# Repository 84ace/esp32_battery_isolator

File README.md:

<!-- PROJECT SHIELDS -->
<!--
*** I'm using markdown "reference style" links for readability.
*** Reference links are enclosed in brackets [ ] instead of parentheses ( ).
*** See the bottom of this document for the declaration of the reference variables
*** for contributors-url, forks-url, etc. This is an optional, concise syntax you may use.
*** https://www.markdownguide.org/basic-syntax/#reference-style-links
-->
[![Contributors][contributors-shield]][contributors-url]
[![Forks][forks-shield]][forks-url]
[![Stargazers][stars-shield]][stars-url]
[![Issues][issues-shield]][issues-url]
[![MIT License][license-shield]][license-url]
[![LinkedIn][linkedin-shield]][linkedin-url]

<!-- PROJECT LOGO -->
<br />
<p align="center">

  <h3 align="center">ESP32 Battery Isolator</h3>

  <p align="center">
    Off-road battery management
    <br />
    <a href="https://github.com/84ace/esp32_battery_isolator/wiki"><strong>Explore the docs »</strong></a>
    <br />
    <br />
    <a href="https://github.com/84ace/esp32_battery_isolator/tree/master/board_images">Board Images</a>
    ·
    <a href="https://github.com/84ace/esp32_battery_isolator/issues">Report Bug</a>
    ·
    <a href="https://github.com/84ace/esp32_battery_isolator/issues">Request Feature</a>
  </p>
</p>

<!-- TABLE OF CONTENTS -->
<details open="open">
  <summary>Table of Contents</summary>
  <ol>
    <li>
      <a href="#about-the-project">About The Project</a>
      <ul>
        <li><a href="#main-features">Main Features</a></li>
        <li><a href="#whats-missing">What's Missing</a></li>
      </ul>
    </li>
    <li>
      <a href="#get-the-isolator">Get the Isolator</a>
    </li>
    <li><a href="#roadmap">Roadmap</a></li>
    <li><a href="#contributing">Contributing</a></li>
    <li><a href="#made-with">Made with</a></li>
    <li><a href="#license">License</a></li>
    <li><a href="#contact">Contact</a></li>
    <li><a href="#acknowledgements">Acknowledgements</a></li>
  </ol>
</details>

<!-- ABOUT THE PROJECT -->
## About The Project

[![ESP32 Battery Isolator][product-screenshot]](https://github.com/84ace/esp32_battery_isolator/raw/master/enclosure/front_iso.png)

The ESP32 Battery Isolator was created so that I could have better control over battery and load isolation, and because I thought it would be an interesting project that would allow me to learn a few new things. 

I also thought that I should be able to turn the lights off in camp from the comfort of bed, rather than having to turn the lights off and walk to bed in the dark and probably kick my toe.

<!-- MAIN FEATURES -->
## Main Features:
* Dual battery input
* Triple load output
* Charger input (From external MPPT/solar charge controller)
* Current sensors
* Temperature sensor
* 128x32 OLED screen
* Bluetooth (for remote control via phone app)
* WiFi (for debugging)
* USB (micro)
* 30A continuous operation

<!-- WHAT"S MISSING -->
## What's missing:
* A Phone app for remote control / live telemetry

If you would like to contribute an app please contact me via the <a href="https://github.com/84ace/esp32_battery_isolator/tree/master/board_images">issues</a> page.

<!-- GETTING STARTED -->
## Get the Isolator

There are two ways to get started with the ESP32 Battery Isolator: 
* You can either take the easy(er) way and buy a pre-made unit from [here](https://placeholder.com/) 
* you can send the gerber files off to your favourite fab house, order the components, assemble the board and print the enclosure yourself.

Your choice!

<!-- ROADMAP -->
## Roadmap

See the [open issues](https://github.com/84ace/esp32_battery_isolator/issues) for a list of proposed features (and known issues).

<!-- CONTRIBUTING -->
## Contributing

Contributions are what make the open source community such an amazing place to be learn, inspire, and create. Any contributions you make are **greatly appreciated**.

1. Fork the Project
2. Create your Feature Branch (`git checkout -b feature/AmazingFeature`)
3. Commit your Changes (`git commit -m 'Add some AmazingFeature'`)
4. Push to the Branch (`git push origin feature/AmazingFeature`)
5. Open a Pull Request

<!-- MADE WITH -->
## Made With:
* [KiCad - Electronic Design Automation Suite](https://kicad.org/)
* [Fusion360 - CAD Software](https://www.autodesk.com.au/products/fusion-360/overview)
* [JLCPCB - PCB Fabrication Manufacturer](https://jlcpcb.com/)

<!-- LICENSE -->
## License

Distributed under the MIT License. See `LICENSE` for more information.

<!-- CONTACT -->
## Contact

84ace - [@Racea_Quigg](https://twitter.com/@RaceaQuigg)

Project Link: [https://github.com/84ace/esp32_battery_isolator](https://github.com/84ace)

<!-- MARKDOWN LINKS & IMAGES -->
<!-- https://www.markdownguide.org/basic-syntax/#reference-style-links -->
[contributors-shield]: https://img.shields.io/github/contributors/84ace/esp32_battery_isolator.svg?style=for-the-badge
[contributors-url]: https://github.com/84ace/esp32_battery_isolator/graphs/contributors
[forks-shield]: https://img.shields.io/github/forks/84ace/esp32_battery_isolator.svg?style=for-the-badge
[forks-url]: https://github.com/84ace/esp32_battery_isolator/network/members
[stars-shield]: https://img.shields.io/github/stars/84ace/esp32_battery_isolator.svg?style=for-the-badge
[stars-url]: https://github.com/84ace/esp32_battery_isolator/stargazers
[issues-shield]: https://img.shields.io/github/issues/84ace/esp32_battery_isolator.svg?style=for-the-badge
[issues-url]: https://github.com/84ace/esp32_battery_isolator/issues
[license-shield]: https://img.shields.io/github/license/84ace/esp32_battery_isolator.svg?style=for-the-badge
[license-url]: https://github.com/84ace/esp32_battery_isolator/blob/master/LICENSE.txt
[linkedin-shield]: https://img.shields.io/badge/-LinkedIn-black.svg?style=for-the-badge&logo=linkedin&colorB=555
[linkedin-url]: https://www.linkedin.com/in/acea-quigg-2007036b/
[product-screenshot]: enclosure/front_iso.png

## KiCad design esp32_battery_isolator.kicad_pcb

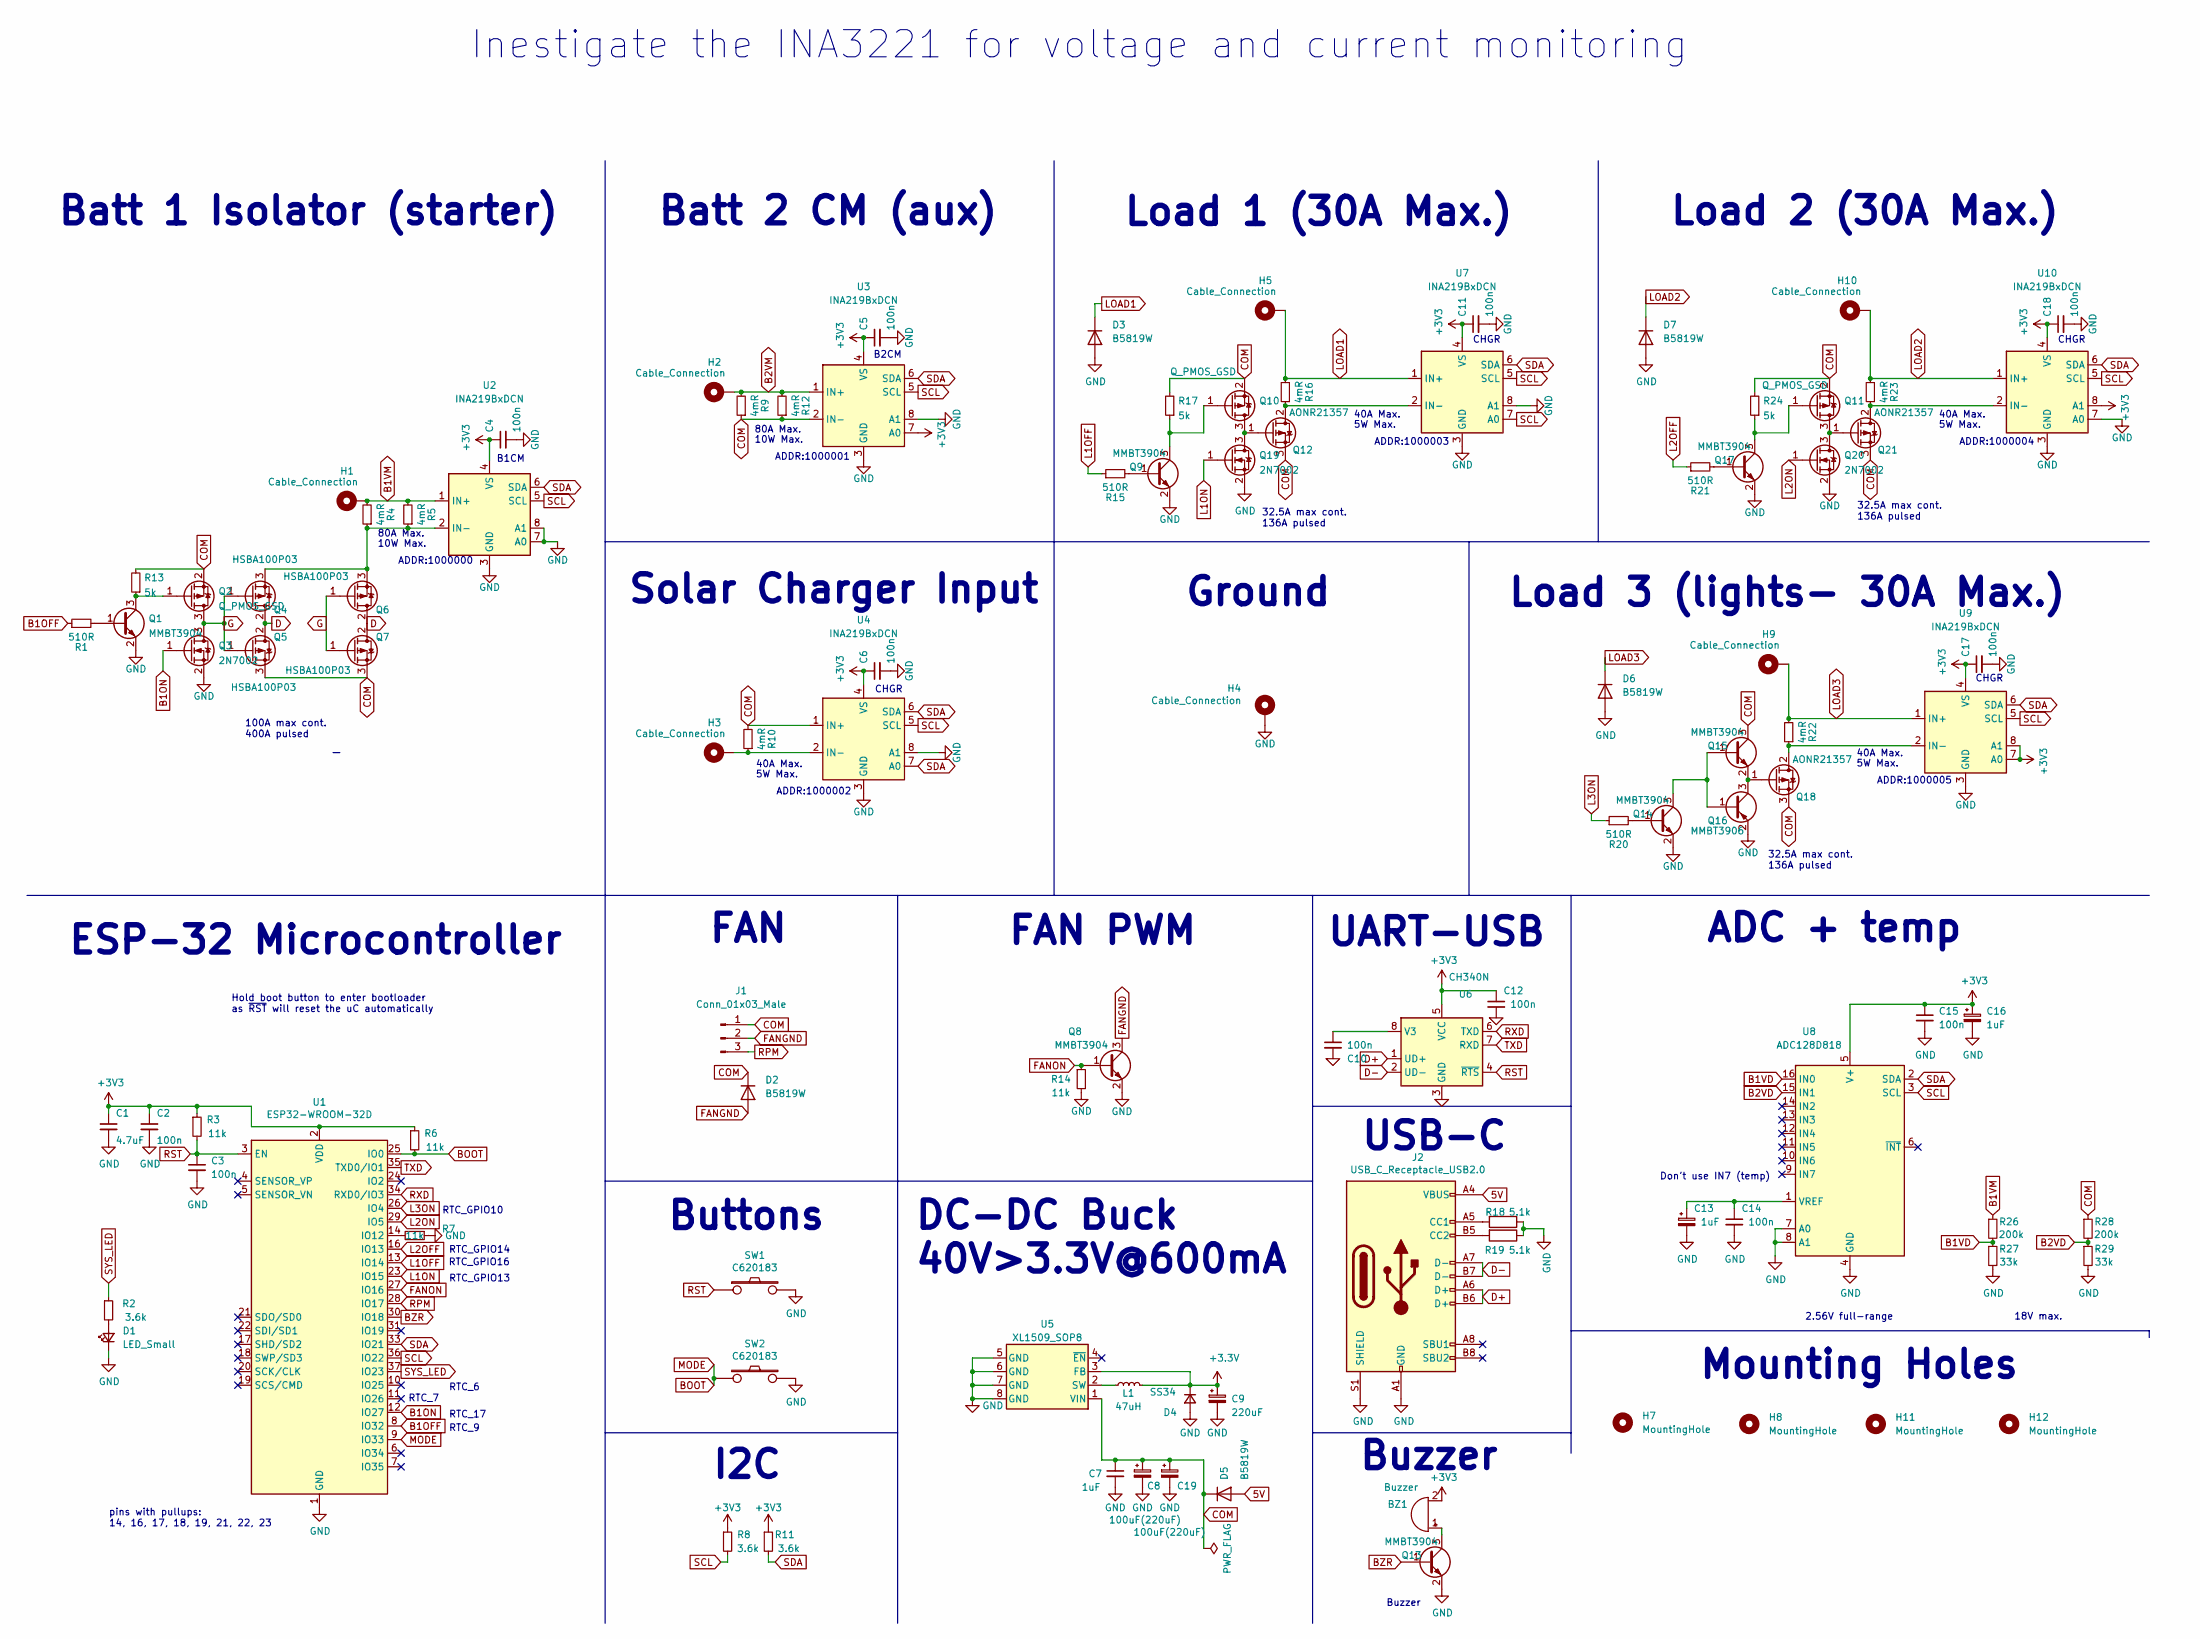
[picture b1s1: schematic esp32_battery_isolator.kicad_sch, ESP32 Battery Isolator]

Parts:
BZ1: Buzzer; SMDBuzzer_C201046; lcsc_part_number C201046
C1: 4.7uF; C_0805_2012Metric; lcsc_part_number C1779
C2, C3, C4, C5, C6, C10, C11, C12, C14, C15, C17, C18: 100n; C_0603_1608Metric; lcsc_part_number C14663
C7: 1uF; C_0603_1608Metric; lcsc_part_number C15849
C8, C19: 100uF(220uF); C_Elec_6.3x5.4; lcsc_part_number C696189
C9: 220uF; CP_EIA-3528-15_AVX-H; lcsc_part_number C30242
C13, C16: 1uF; CP_EIA-3528-21_Kemet-B; lcsc_part_number C169224
D1: LED_Small; LED_0603_1608Metric; lcsc_part_number C2286
D2, D5: B5819W; D_SOD-123; lcsc_part_number C8598
D3, D6, D7: B5819W; D_SMC; lcsc_part_number C211777
D4: SS34; D_SMA; lcsc_part_number C8678
H1, H2, H3, H4, H5, H9, H10: Cable_Connection; Rivneut_M6_Via
H7, H8, H11, H12: MountingHole; MountingHole_3.2mm_M3_Pad_Via
J1: Conn_01x03_Male; JST_SH_SM03B-SRSS-TB_1x03-1MP_P1.00mm_Horizontal; lcsc_part_number C160403
J2: USB_C_Receptacle_USB2.0; USB_C_Receptacle_HRO_TYPE-C-31-M-12; mfr_part_number TYPE-C-31-M-12; lcsc_part_number C165948
L1: 47uH; L_Bourns_SRN6045TA; lcsc_part_number C36414
Q1, Q8, Q9, Q13, Q14, Q15, Q17: MMBT3904; SOT-23; mfr_part_number MMBT3904; lcsc_part_number C20526
Q2, Q10, Q11: Q_PMOS_GSD; SOT-23
Q3, Q19, Q20: 2N7002; SOT-23
Q4, Q5, Q6, Q7: HSBA100P03; LFPAK56; lcsc_part_number C701057
Q12, Q18, Q21: AONR21357; DFN-TRANS_AONR21321; lcsc_part_number C431196
Q16: MMBT3906; SOT-23; lcsc_part_number C111114
R1, R15, R20, R21: 510R; R_0603_1608Metric; lcsc_part_number C269885
R2, R8, R11: 3.6k; R_0603_1608Metric; lcsc_part_number C22980
R3, R6, R7, R14: 11k; R_0603_1608Metric; lcsc_part_number C25950
R4, R5, R9, R10, R12, R16, R22, R23: 4mR; RS1050Metric_Pad5.3x2.5mm; lcsc_part_number C481476
R13, R17, R24: 5k; R_0603_1608Metric; lcsc_part_number C269885
R18, R19: 5.1k; R_0603_1608Metric; mfr_part_number RS-03K5101FT; lcsc_part_number C156350
R26, R28: 200k; R_0603_1608Metric; lcsc_part_number C25811
R27, R29: 33k; R_0603_1608Metric; lcsc_part_number C4216
SW1, SW2: C620183; TS4550TP; lcsc_part_number C620183
U1: ESP32-WROOM-32D; ESP32-WROOM-32; mfr_part_number ESP32-WROOM-32D; lcsc_part_number C473012
U2, U3, U4, U7, U9, U10: INA219BxDCN; SOT-23-8; lcsc_part_number C2155693
U5: XL1509_SOP8; SOIC-8_3.9x4.9mm_P1.27mm; lcsc_part_number C2681226
U6: CH340N; SOIC-8_3.9x4.9mm_P1.27mm; mfr_part_number CH340N; lcsc_part_number C506813
U8: ADC128D818; TSSOP-16_4.4x5mm_P0.65mm; mfr_part_number ADC128D818CIMTX; lcsc_part_number C139062

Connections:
5V: D5.2 (A), J2.A4 (VBUS), J2.A9 (VBUS), J2.B4 (VBUS), J2.B9 (VBUS)
B1OFF: R1.1, U1.8 (IO32)
B1ON: Q3.1 (G), U1.12 (IO27)
B1VD: R26.2, R27.1, U8.16 (IN0)
B1VM: H1.1, R4.2, R5.2, R26.1, U2.1 (IN+)
B2VD: R28.2, R29.1, U8.15 (IN1)
B2VM: H2.1, R9.2, R12.2, U3.1 (IN+)
BOOT: R6.2, SW2.1, U1.9 (IO33), U1.25 (IO0)
BZR: Q13.1 (B), U1.30 (IO18)
COM: C7.1, C8.1, C19.1, D2.1 (K), D5.1 (K), J1.1, Q2.2 (S), Q5.3 (S), Q7.3 (S), Q10.2 (S), Q11.2 (S), Q12.3 (S), Q15.3 (C), Q18.3 (S), Q21.3 (S), R9.1, R10.2, R12.1, R13.2, R17.2, R24.2, R28.1, U3.2 (IN-), U4.1 (IN+), U5.1 (VIN)
D: Q4.2 (D), Q5.2 (D), Q6.2 (D), Q7.2 (D)
D+: J2.A6 (D+), J2.B6 (D+), U6.1 (UD+)
D-: J2.A7 (D-), J2.B7 (D-), U6.2 (UD-)
FANGND: D2.2 (A), J1.2, Q8.3 (C)
FANON: Q8.1 (B), R14.1, U1.27 (IO16)
G: Q2.3 (D), Q3.3 (D), Q4.1 (G), Q5.1 (G), Q6.1 (G), Q7.1 (G)
GND: C1.2, C2.2, C3.2, C4.2, C5.2, C6.2, C7.2, C8.2, C9.2, C10.2, C11.2, C12.2, C13.2, C14.2, C15.2, C16.2, C17.2, C18.2, C19.2, D1.1 (K), D3.2 (A), D4.2 (A), D6.2 (A), D7.2 (A), H4.1, J2.A1 (GND), J2.A12 (GND), J2.B1 (GND), J2.B12 (GND), J2.S1 (SHIELD), Q1.2 (E), Q3.2 (S), Q8.2 (E), Q9.2 (E), Q13.2 (E), Q14.2 (E), Q16.2 (E), Q17.2 (E), Q19.2 (S), Q20.2 (S), R7.1, R14.2, R18.1, R19.1, R27.2, R29.2, SW1.2, SW2.2, U1.1 (GND), U1.15 (GND), U1.38 (GND), U1.39 (GND), U2.3 (GND), U2.7 (A0), U2.8 (A1), U3.3 (GND), U3.8 (A1), U4.3 (GND), U4.8 (A1), U5.5 (GND), U5.6 (GND), U5.7 (GND), U5.8 (GND), U6.3 (GND), U7.3 (GND), U7.8 (A1), U8.4 (GND), U8.7 (A0), U8.8 (A1), U9.3 (GND), U10.3 (GND), U10.7 (A0)
L1OFF: R15.1, U1.13 (IO14)
L1ON: Q19.1 (G), U1.23 (IO15)
L2OFF: R21.1, U1.16 (IO13)
L2ON: Q20.1 (G), U1.29 (IO5)
L3ON: R20.1, U1.26 (IO4)
LOAD1: D3.1 (K), H5.1, R16.2, U7.1 (IN+)
LOAD2: D7.1 (K), H10.1, R23.2, U10.1 (IN+)
LOAD3: D6.1 (K), H9.1, R22.2, U9.1 (IN+)
unnamed: BZ1.1 (-), Q13.3 (C)
unnamed: D1.2 (A), R2.2
unnamed: J2.A5 (CC1), R18.2
unnamed: J2.B5 (CC2), R19.2
unnamed: Q1.1 (B), R1.2
unnamed: Q1.3 (C), Q2.1 (G), R13.1
unnamed: Q4.3 (S), Q6.3 (S), R4.1, R5.1, U2.2 (IN-)
unnamed: Q9.1 (B), R15.2
unnamed: Q10.3 (D), Q12.1 (G), Q19.3 (D)
unnamed: Q9.3 (C), Q10.1 (G), R17.1
unnamed: Q11.3 (D), Q20.3 (D), Q21.1 (G)
unnamed: Q11.1 (G), Q17.3 (C), R24.1
unnamed: Q12.2 (D), R16.1, U7.2 (IN-)
unnamed: Q14.1 (B), R20.2
unnamed: Q14.3 (C), Q15.1 (B), Q16.1 (B)
unnamed: Q15.2 (E), Q16.3 (C), Q18.1 (G)
unnamed: Q17.1 (B), R21.2
unnamed: Q18.2 (D), R22.1, U9.2 (IN-)
unnamed: Q21.2 (D), R23.1, U10.2 (IN-)
unnamed: R7.2, U1.14 (IO12)
unnamed: H3.1, R10.1, U4.2 (IN-)
unnamed: L1.1, U5.2 (SW)
unnamed: C10.1, U6.8 (V3)
unnamed: C13.1, C14.1, U8.1 (VREF)
RPM: J1.3, U1.28 (IO17)
RST: C3.1, R3.2, SW1.1, U1.3 (EN), U6.4 (~RTS)
RXD: U1.34 (RXD0/IO3), U6.6 (TXD)
SCL: R8.2, U1.36 (IO22), U2.5 (SCL), U3.5 (SCL), U4.5 (SCL), U7.5 (SCL), U7.7 (A0), U8.3 (SCL), U9.5 (SCL), U10.5 (SCL)
SDA: R11.2, U1.33 (IO21), U2.6 (SDA), U3.6 (SDA), U4.6 (SDA), U4.7 (A0), U7.6 (SDA), U8.2 (SDA), U9.6 (SDA), U10.6 (SDA)
SYS_LED: R2.1, U1.37 (IO23)
TXD: U1.35 (TXD0/IO1), U6.7 (RXD)

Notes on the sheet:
RTC_GPIO10
Mounting Holes
40A Max.
Ground
5W Max.
32.5A max cont. 136A pulsed
B2CM
ADDR:1000001
RTC_7
ADDR:1000003
I2C
Hold boot button to enter bootloader as ~{RST} will reset the uC automatically
Inestigate the INA3221 for voltage and current monitoring
ESP-32 Microcontroller
UART-USB
10W Max.
DC-DC Buck 40V>3.3V@600mA
Load 3 (lights- 30A Max.)
ADDR:1000005
ADDR:1000004
Buttons
CHGR
80A Max.
ADDR:1000000
B1CM
RTC_9
ADDR:1000002
Don’t use IN7 (temp)
2.56V full-range
RTC_6
100A max cont. 400A pulsed
Load 2 (30A Max.)
pins with pullups: 14, 16, 17, 18, 19, 21, 22, 23
FAN
RTC_GPIO16
RTC_GPIO14
RTC_17
Batt 1 Isolator (starter)
Solar Charger Input
ADC + temp

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
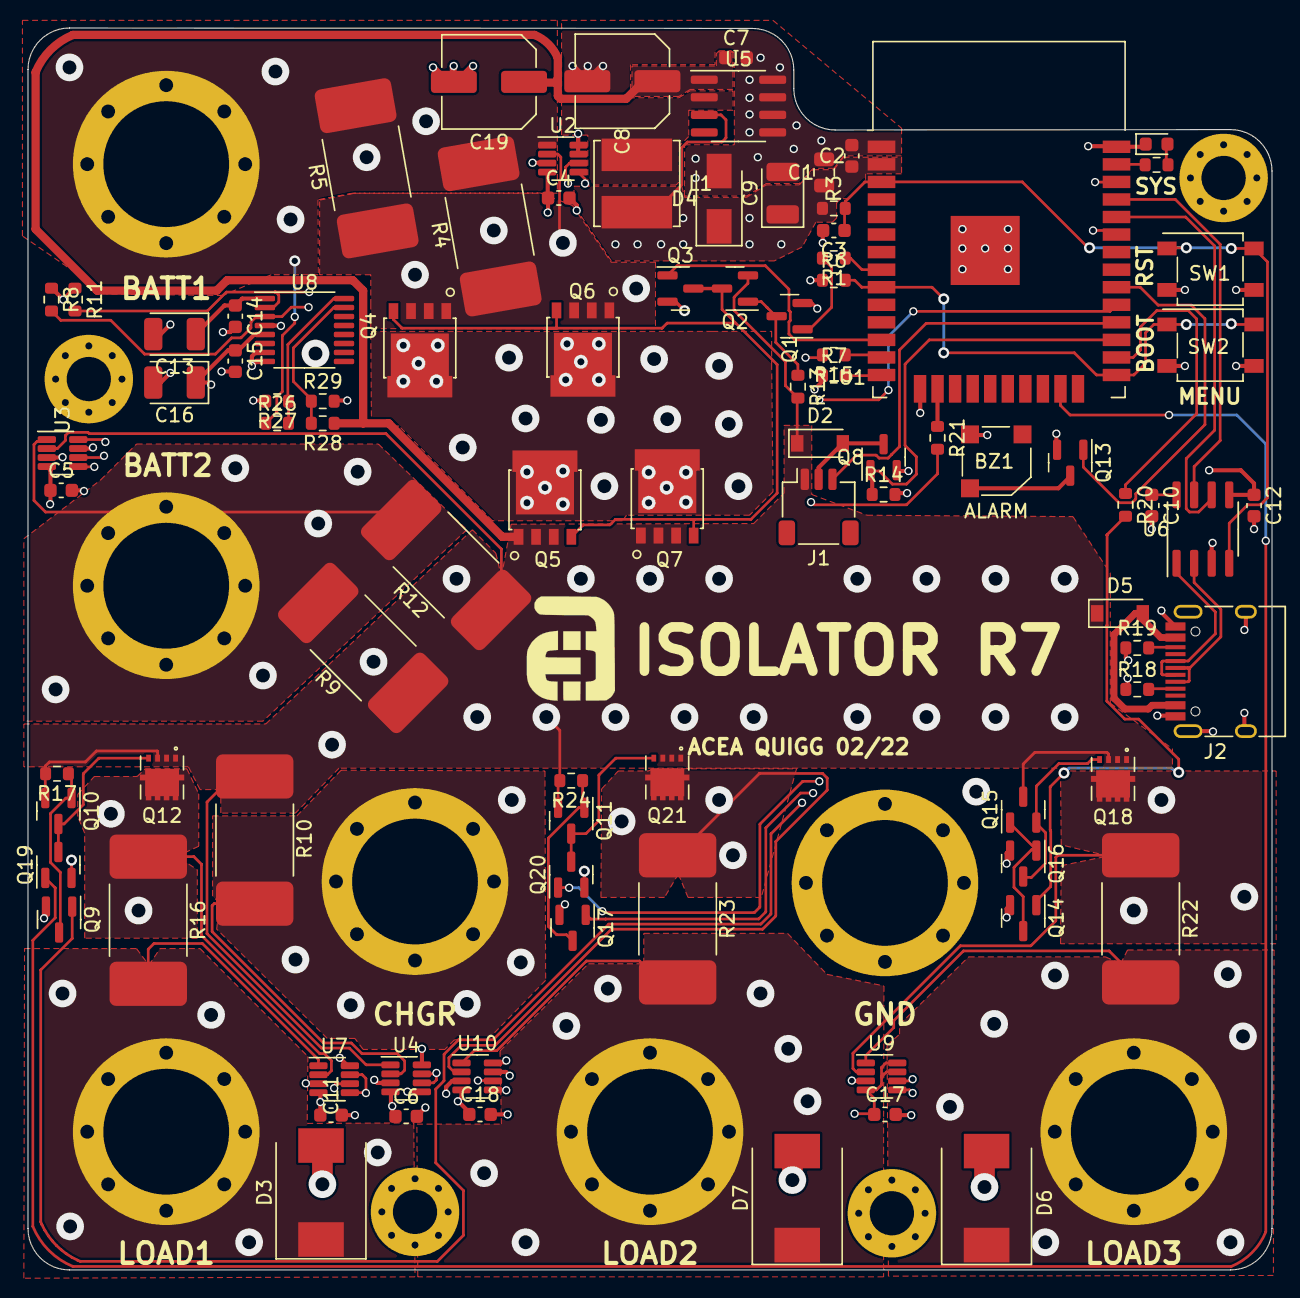
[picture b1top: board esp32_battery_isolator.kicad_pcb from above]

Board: 4 copper layers, 90.0 x 89.9 mm, 103 parts (0 on the bottom side), 57 nets.

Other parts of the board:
Ref**: Val**; aces_electronics_small

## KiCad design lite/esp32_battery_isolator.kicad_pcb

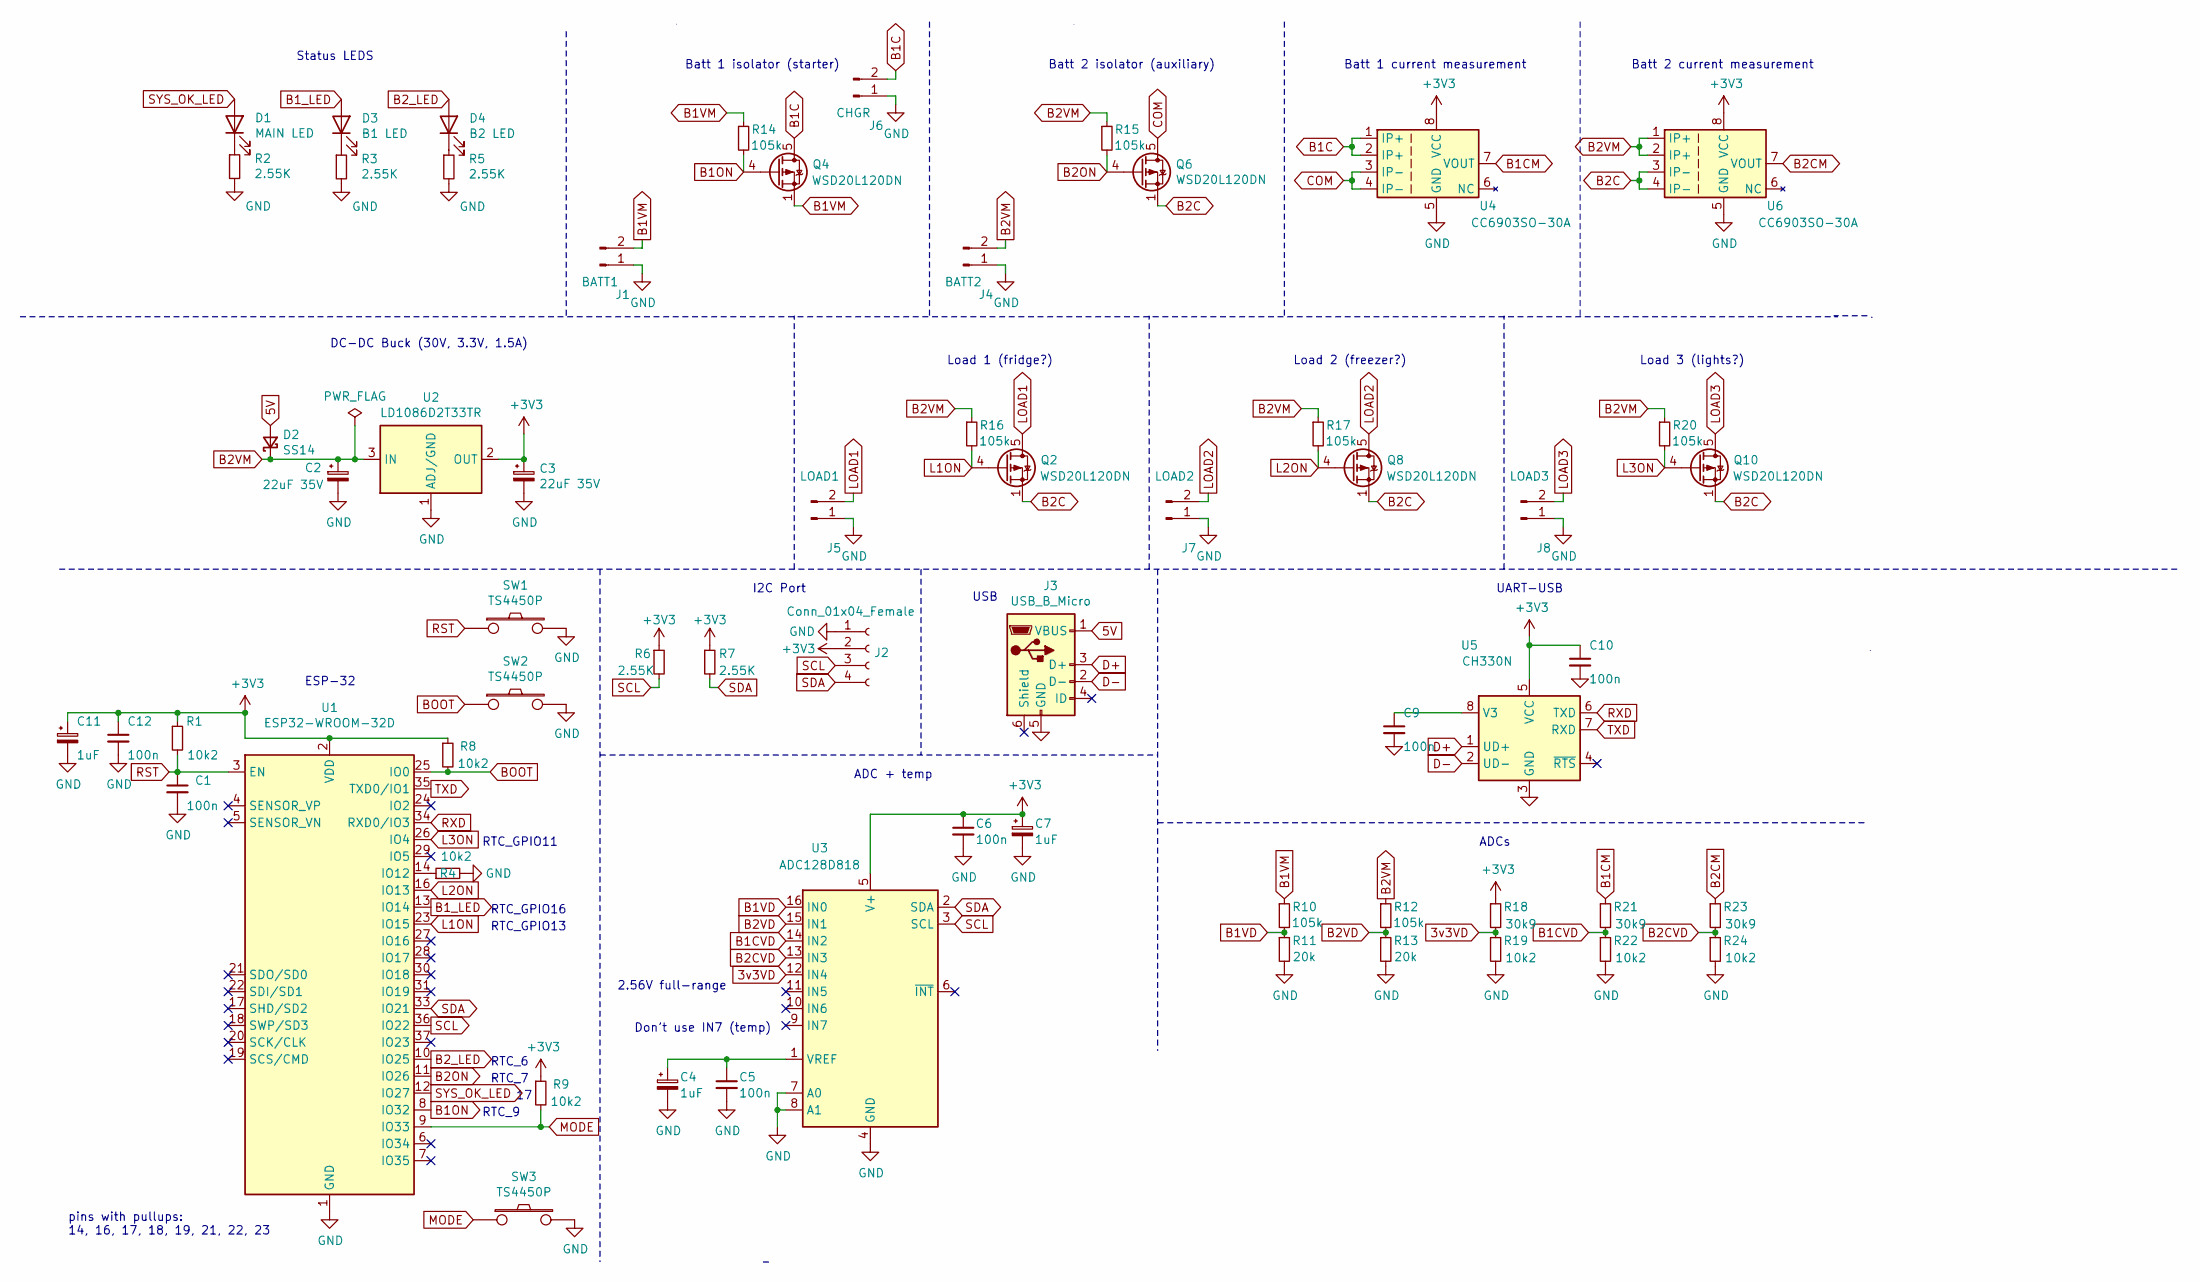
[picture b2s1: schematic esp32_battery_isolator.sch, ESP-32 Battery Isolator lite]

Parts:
C1, C5, C6, C9, C10, C12: 100n; C_0805_2012Metric; mfr_part_number 0805B104K250; lcsc_part_number C128353
C2, C3: 22uF 35V; C_Elec_5x5.4; mfr_part_number RVT1V220M0505; lcsc_part_number C23289
C4, C7, C11: 1uF; CP_EIA-3216-18_Kemet-A; mfr_part_number CA45-A035K105T; lcsc_part_number C126949
D1: MAIN LED; LED_0603_1608Metric; mfr_part_number 19-217/R6C-AL1M2VY/3T; lcsc_part_number C72044
D2: SS14; D_SMA; mfr_part_number SS14; lcsc_part_number C2480
D3: B1 LED; LED_0603_1608Metric; mfr_part_number 19-217/R6C-AL1M2VY/3T; lcsc_part_number C72044
D4: B2 LED; LED_0603_1608Metric; mfr_part_number 19-217/R6C-AL1M2VY/3T; lcsc_part_number C72044
J1: BATT1; AMASS_XT60-F_1x02_P7.20mm_Vertical
J2: Conn_01x04_Female; PinSocket_1x04_P2.54mm_Vertical
J3: USB_B_Micro; USB_Micro-B_XKB_4BH89_SMT; mfr_part_number U253-051T-4BH89-F1B; lcsc_part_number C319172
J4: BATT2; AMASS_XT60-F_1x02_P7.20mm_Vertical
J5: LOAD1; AMASS_XT60-F_1x02_P7.20mm_Vertical
J6: CHGR; AMASS_XT60-F_1x02_P7.20mm_Vertical
J7: LOAD2; AMASS_XT60-F_1x02_P7.20mm_Vertical
J8: LOAD3; AMASS_XT60-F_1x02_P7.20mm_Vertical
Q2, Q4, Q6, Q8, Q10: WSD20L120DN; PowerPAK_SO-8_Single; mfr_part_number WSD20L120DN; lcsc_part_number C148395
R1, R4, R8, R9, R19, R22, R24: 10k2; R_0603_1608Metric; mfr_part_number RT0603BRE0710K2L; lcsc_part_number C705802
R2, R3, R5, R6, R7: 2.55K; LED_0603_1608Metric; mfr_part_number RS-03K2551FT; lcsc_part_number C304726
R10, R12, R14, R15, R16, R17, R20: 105k; R_0603_1608Metric; mfr_part_number ERA3AEB1053V; lcsc_part_number C491109
R11, R13: 20k; R_0603_1608Metric; mfr_part_number AR03BTCX2002; lcsc_part_number C319766
R18, R21, R23: 30k9; R_0603_1608Metric; mfr_part_number 0603WAF3092T5E; lcsc_part_number C23022
SW1, SW2, SW3: TS4450P; TS4550TP; mfr_part_number TS4550TP; lcsc_part_number C412373
U1: ESP32-WROOM-32D; ESP32-WROOM-32; mfr_part_number ESP32-WROOM-32D; lcsc_part_number C473012
U2: LD1086D2T33TR; TO-252-2; mfr_part_number LD1086DT33TR; lcsc_part_number C12051
U3: ADC128D818; TSSOP-16_4.4x5mm_P0.65mm; mfr_part_number ADC128D818CIMTX; lcsc_part_number C139062
U4, U6: CC6903SO-30A; SOP-8_3.9x4.9mm_P1.27mm; mfr_part_number CC6903SO-30A; lcsc_part_number C469388
U5: CH330N; SOIC-8_3.9x4.9mm_P1.27mm; mfr_part_number CH330N; lcsc_part_number C108996

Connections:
3v3VD: R18.2, R19.1, U3.12 (IN4)
5V: D2.2 (A), J3.1 (VBUS)
+3V3: C3.1, C6.1, C7.1, C10.1, C11.1, C12.1, J2.2, R1.1, R6.1, R7.1, R8.1, R9.1, R18.1, U1.2 (VDD), U2.2 (OUT), U3.5 (V+), U4.8 (VCC), U5.5 (VCC), U6.8 (VCC)
B1C: J6.2, Q4.5 (D), U4.1 (IP+), U4.2 (IP+)
B1CM: R21.1, U4.7 (VOUT)
B1CVD: R21.2, R22.1, U3.14 (IN2)
B1ON: Q4.4 (G), R14.2, U1.8 (IO32)
B1VD: R10.2, R11.1, U3.16 (IN0)
B1VM: J1.2, Q4.1 (S), Q4.2 (S), Q4.3 (S), R10.1, R14.1
B1_LED: D3.2 (A), U1.13 (IO14)
B2C: Q2.1 (S), Q2.2 (S), Q2.3 (S), Q6.1 (S), Q6.2 (S), Q6.3 (S), Q8.1 (S), Q8.2 (S), Q8.3 (S), Q10.1 (S), Q10.2 (S), Q10.3 (S), U6.3 (IP-), U6.4 (IP-)
B2CM: R23.1, U6.7 (VOUT)
B2CVD: R23.2, R24.1, U3.13 (IN3)
B2ON: Q6.4 (G), R15.2, U1.11 (IO26)
B2VD: R12.2, R13.1, U3.15 (IN1)
B2VM: C2.1, D2.1 (K), J4.2, R12.1, R15.1, R16.1, R17.1, R20.1, U2.3 (IN), U6.1 (IP+), U6.2 (IP+)
B2_LED: D4.2 (A), U1.10 (IO25)
BOOT: R8.2, SW2.1, U1.25 (IO0)
COM: Q6.5 (D), U4.3 (IP-), U4.4 (IP-)
D+: J3.3 (D+), U5.1 (UD+)
D-: J3.2 (D-), U5.2 (UD-)
GND: C1.2, C2.2, C3.2, C4.2, C5.2, C6.2, C7.2, C9.2, C10.2, C11.2, C12.2, J1.1, J2.1, J3.5 (GND), J4.1, J5.1, J6.1, J7.1, J8.1, R2.2, R3.2, R4.2, R5.2, R11.2, R13.2, R19.2, R22.2, R24.2, SW1.2, SW2.2, SW3.2, U1.1 (GND), U1.15 (GND), U1.38 (GND), U1.39 (GND), U2.1 (ADJ/GND), U3.4 (GND), U3.7 (A0), U3.8 (A1), U4.5 (GND), U5.3 (GND), U6.5 (GND)
L1ON: Q2.4 (G), R16.2, U1.23 (IO15)
L2ON: Q8.4 (G), R17.2, U1.16 (IO13)
L3ON: Q10.4 (G), R20.2, U1.26 (IO4)
LOAD1: J5.2, Q2.5 (D)
LOAD2: J7.2, Q8.5 (D)
LOAD3: J8.2, Q10.5 (D)
MODE: R9.2, SW3.1, U1.9 (IO33)
unnamed: C4.1, C5.1, U3.1 (VREF)
unnamed: C9.1, U5.8 (V3)
unnamed: D1.1 (K), R2.1
unnamed: D3.1 (K), R3.1
unnamed: D4.1 (K), R5.1
unnamed: R4.1, U1.14 (IO12)
RST: C1.1, R1.2, SW1.1, U1.3 (EN)
RXD: U1.34 (RXD0/IO3), U5.6 (TXD)
SCL: J2.3, R6.2, U1.36 (IO22), U3.3 (SCL)
SDA: J2.4, R7.2, U1.33 (IO21), U3.2 (SDA)
SYS_OK_LED: D1.2 (A), U1.12 (IO27)
TXD: U1.35 (TXD0/IO1), U5.7 (RXD)

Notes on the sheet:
Status LEDS
ESP-32
ADCs
I2C Port
DC-DC Buck (30V, 3.3V, 1.5A)
2.56V full-range
ADC + temp
USB
UART-USB
Batt 1 isolator (starter)
Batt 2 current measurement
Don’t use IN7 (temp)
Batt 1 current measurement
Load 1 (fridge?)
Load 2 (freezer?)
Load 3 (lights?)
Batt 2 isolator (auxiliary)
pins with pullups: 14, 16, 17, 18, 19, 21, 22, 23
RTC_GPIO11
RTC_GPIO16
RTC_6
RTC_9
RTC_GPIO13
RTC_7

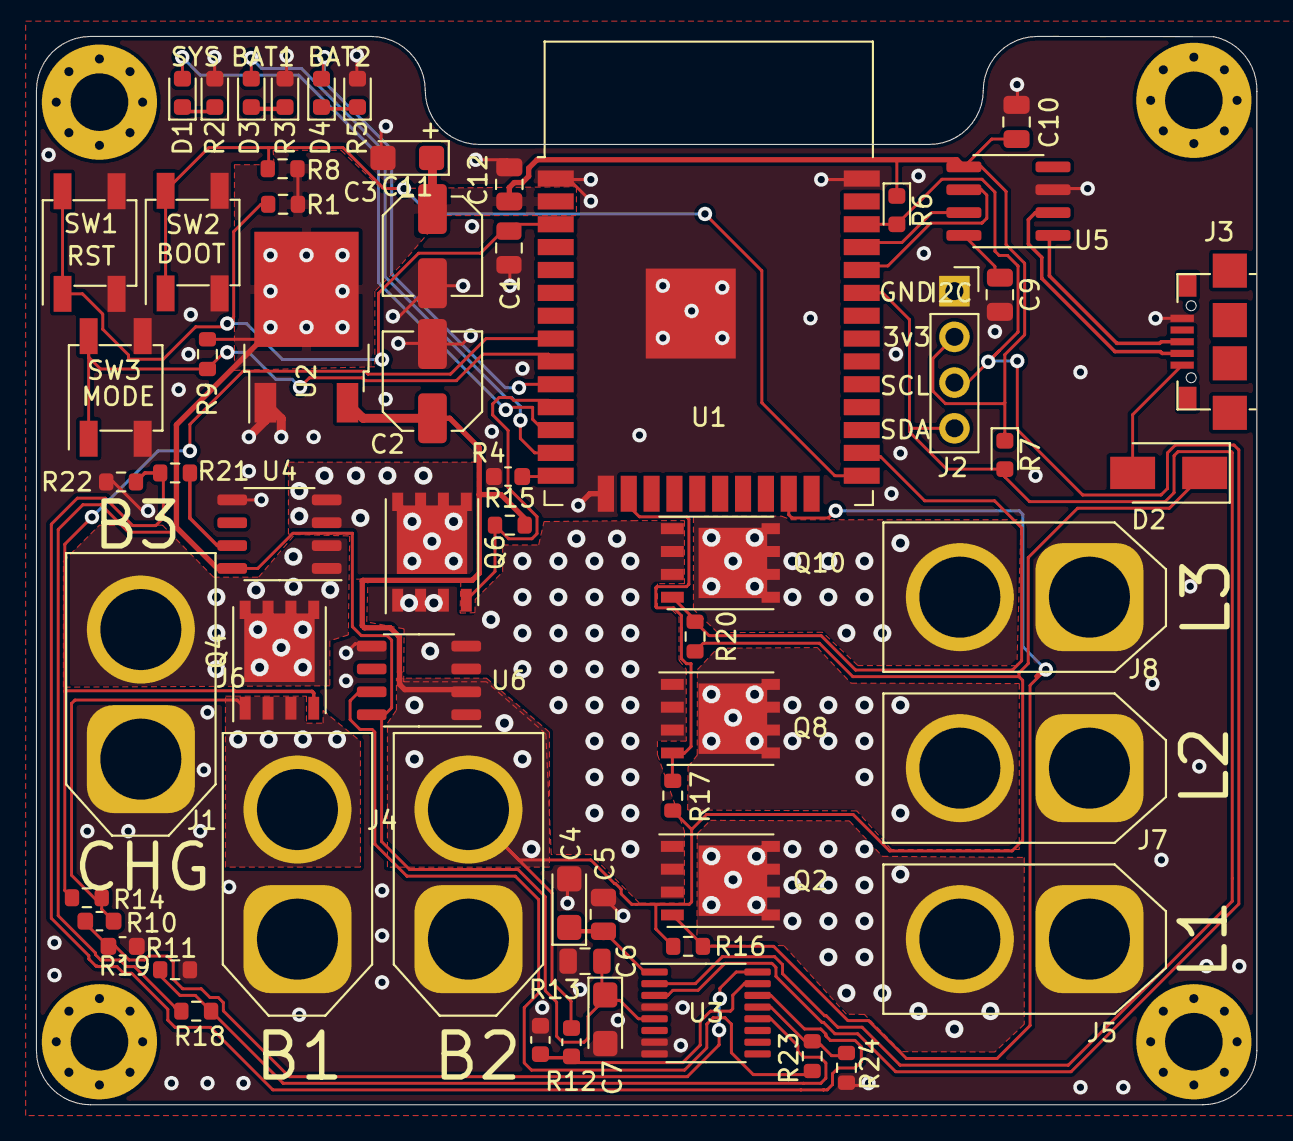
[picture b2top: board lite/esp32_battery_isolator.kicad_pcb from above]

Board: 2 copper layers, 67.8 x 59.3 mm, 65 parts (0 on the bottom side), 41 nets.

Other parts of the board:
H1, H1#2, H1#3, H1#4: MountingHole_3.2mm_M3_Pad_Via

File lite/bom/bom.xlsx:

References | lcsc_part_number | mfr_part_number | package | Value | Footprint | Quantity
BI:C1, C5, C6, C12, C9, C10 | C128353 | 0805B104K250 | 0805 | 100n | C_0805_2012Metric | 6
BI:C2, C3 | C23289 | RVT1V220M0505 | 5x5.4 | 22uF 35V | C_Elec_5x5.4 | 2
BI:C4, C7, C11 | C126949 | CA45-A035K105T | CASE_A_3216 | 1uF | CP_EIA-3216-18_Kemet-A | 3
BI:D1, D3, D4 | C72044 | 19-217/R6C-AL1M2VY/3T | 0603 | RED LEDs | LED_0603_1608Metric | 1
BI:D2 | C2480 | SS14 | SMA | SS14 | D_SMA | 1
BI:J3 | C319172 | U253-051T-4BH89-F1B | micro_usb | USB_B_Micro | USB_Micro-B_XKB_4BH89_SMT | 1
BI:J1,J4, J6 | C98733 | XT60-F |  | BATT2 | AMASS_XT60-F_1x02_P7.20mm_Vertical | 3
BI:J5, J7, J8 | C98734 | XT60-M |  | LOAD1 | AMASS_XT60-M_1x02_P7.20mm_Vertical | 3
BI:Q2, Q4, Q6, Q8, Q10 | C148395 | WSD20L120DN | SON8 | WSD20L120DN | PowerPAK_SO-8_Single | 5
BI:R1, R4, R8, R9, R19, R22, R24 | C705802 | RT0603BRE0710K2L | 0603 | 10k2 | R_0603_1608Metric | 7
BI:R10, R12, R14, R15, R16, R17, R20 | C491109 | ERA3AEB1053V | 0603 | 105k | R_0603_1608Metric | 7
BI:R11, R13 | C319766 | AR03BTCX2002 | 0603 | 20k | R_0603_1608Metric | 2
BI:R18, R21, R23 | C23022 | 0603WAF3092T5E | 0603 | 30k9 | R_0603_1608Metric | 3
BI:R2, R3, R5, R6, R7 | C304726 | RS-03K2551FT | 0603 | 2.55K | LED_0603_1608Metric | 3
BI:SW1, SW2, SW3 | C72443 | KMR221GLFS | KMR2 | KMR221GLFS | SW_Push_1P1T_NO_CK_KMR2 | 3
BI:U1 | C473012 | ESP32-WROOM-32D | SMD-38 | ESP32-WROOM-32D | ESP32-WROOM-32 | 1
BI:U2 | C12051 | LD1086DT33TR | TO-252-2(DPAK) | LD1086D2T33TR | TO-252-2 | 1
BI:U3 | C139062 | ADC128D818CIMTX | TSSOP-16 | ADC128D818 | TSSOP-16_4.4x5mm_P0.65mm | 1
BI:U4, U6 | C469388 | CC6903SO-30A\r | SOP-8 | CC6903SO-30A | SOP-8_3.9x4.9mm_P1.27mm | 2
BI:U5 | C108996 | CH330N | SOP-8 | CH330N | SOIC-8_3.9x4.9mm_P1.27mm | 1

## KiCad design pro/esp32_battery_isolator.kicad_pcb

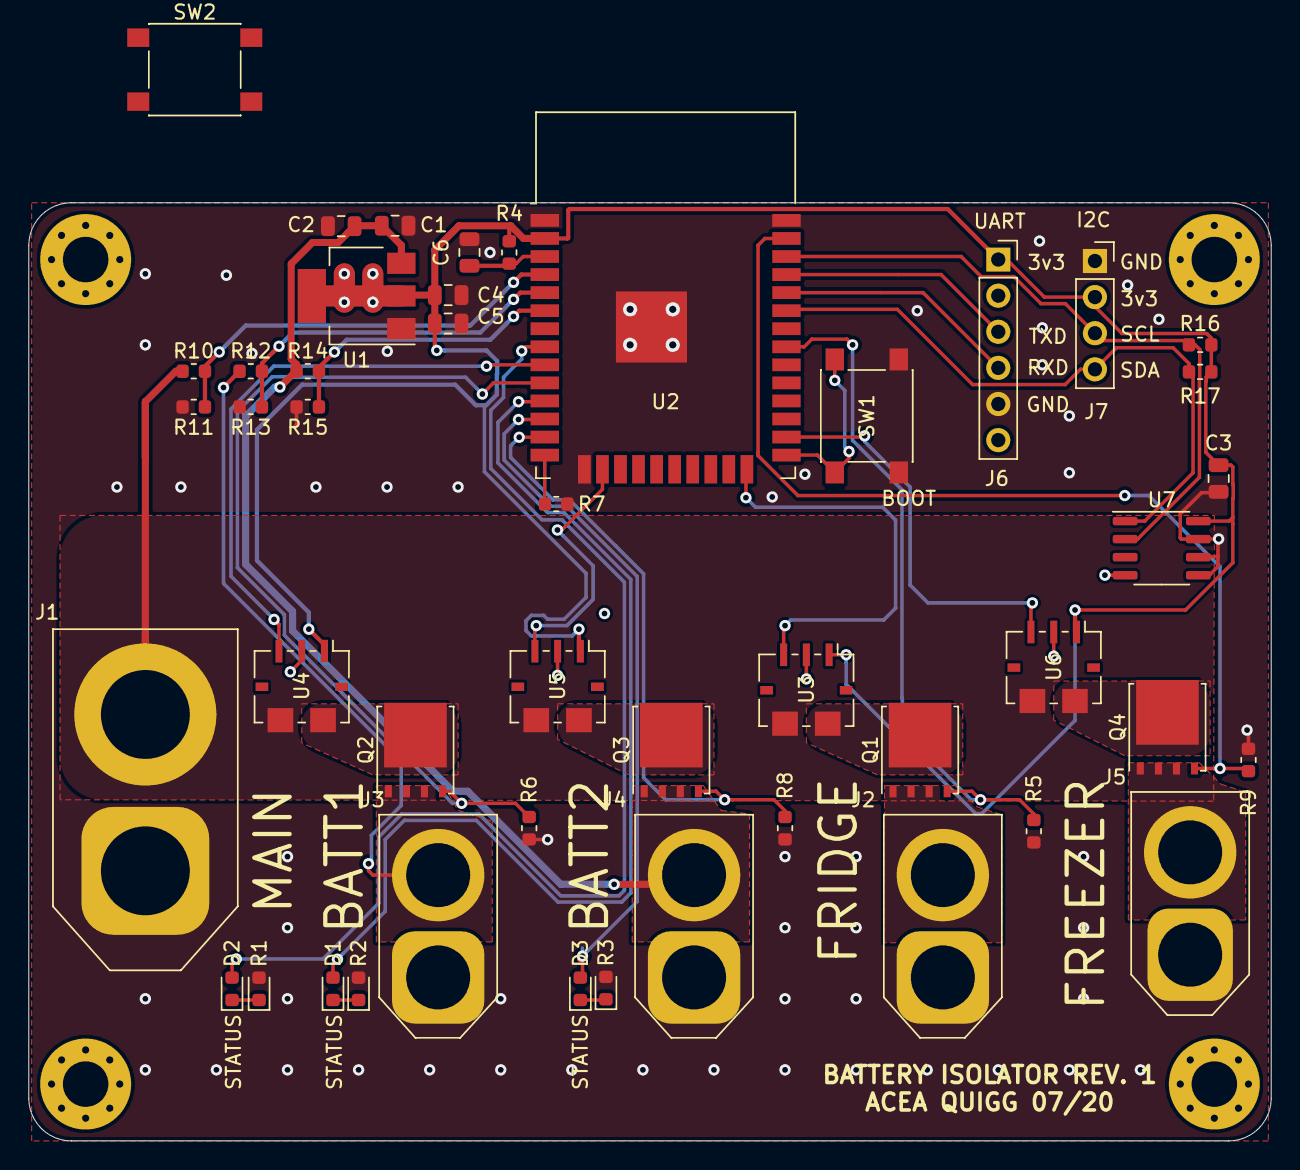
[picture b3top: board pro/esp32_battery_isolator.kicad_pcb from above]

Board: 2 copper layers, 87.4 x 66.0 mm, 50 parts (0 on the bottom side), 35 nets.

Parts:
C1, C4: 10uF; C_0805_2012Metric
C2, C3, C5, C6: 100n; C_0805_2012Metric
D1: AUX1 LED; LED_0603_1608Metric
D2: MAIN LED; LED_0603_1608Metric
D3: AUX2 LED; LED_0603_1608Metric
H1, H1#2, H1#3, H1#4: MountingHole_3.2mm_M3_Pad_Via
J1: INPUT; AMASS_XT90-F_1x02_P11mm_Vertical
J2: LOAD1; AMASS_XT60-F_1x02_P7.20mm_Vertical
J3: BATT1; AMASS_XT60-F_1x02_P7.20mm_Vertical
J4: BATT2; AMASS_XT60-F_1x02_P7.20mm_Vertical
J5: LOAD2; AMASS_XT60-F_1x02_P7.20mm_Vertical
J6: Conn_01x06_Female; PinSocket_1x06_P2.54mm_Vertical
J7: Conn_01x04_Female; PinSocket_1x04_P2.54mm_Vertical
Q1, Q2, Q3, Q4: BSC070N10LS5; TDSON-8-1
R1, R2, R3: 2.55K; LED_0603_1608Metric
R4, R5, R6, R7, R8, R9: 10k; R_0603_1608Metric
R10, R12, R14: 100k; R_0603_1608Metric
R11, R13, R15: 27k; R_0603_1608Metric
R16, R17: 2.2k; R_0603_1608Metric
SW1, SW2: TS-1102W-4316; SW_Push_1P1T_NO_6x6mm_H9.5mm
U1: AMS1117-3.3; SOT-223-3_TabPin2
U2: ESP32-WROOM-32D; ESP32-WROOM-32
U3, U4, U5, U6: ACS781LLRTR-050B; Allegro_PSOF-7_4.8x6.4mm_P1.60mm
U7: LM75BDP,118; SO-8_3.9x4.9mm_P1.27mm

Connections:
+3V3: C3.1, C4.1, C5.1, J6.1, J7.2, R4.1, R16.1, R17.1, U1.2, U2.2, U3.1, U4.1, U5.1, U6.1, U7.8
AUX1_LED: D1.2, U2.11
AUX2_LED: D3.2, U2.12
AUX_1: Q2.4, R6.1, U2.10
AUX_1_C: U2.9, U4.3
AUX_2: Q3.4, R8.1, U2.13
AUX_2_C: U2.16, U5.3
Alternator: J1.2, R10.1, U3.5, U4.5, U5.5, U6.5
BAT1: R12.2, R13.1, U2.5
BAT1V: J3.2, Q2.1, Q2.2, Q2.3, R12.1
BAT2: R14.2, R15.1, U2.6
BAT2V: C1.1, C2.1, J4.2, Q3.1, Q3.2, Q3.3, R14.1, U1.3
GND: C1.2, C2.2, C3.2, C4.2, C5.2, C6.2, J1.1, J2.1, J3.1, J4.1, J5.1, J6.5, J7.1, R1.2, R2.2, R3.2, R5.2, R6.2, R7.1, R8.2, R9.2, R11.2, R13.2, R15.2, SW1.2, SW2.2, U1.1, U2.1, U2.15, U2.38, U2.39, U3.2, U4.2, U5.2, U6.2, U7.4, U7.5, U7.6, U7.7
LOAD_1: Q1.4, R5.1, U2.31
LOAD_1_C: U2.24, U3.3
LOAD_2: Q4.4, R9.1, U2.37
LOAD_2_C: U2.26, U6.3
MAIN: R10.2, R11.1, U2.4
MAIN_LED: D2.2, U2.8
unnamed: D1.1, R2.1
unnamed: D2.1, R1.1
unnamed: D3.1, R3.1
unnamed: J2.2, Q1.1, Q1.2, Q1.3
unnamed: J5.2, Q4.1, Q4.2, Q4.3
unnamed: Q1.5, U3.6
unnamed: Q2.5, U4.6
unnamed: Q3.5, U5.6
unnamed: Q4.5, U6.6
unnamed: R7.2, U2.14
unnamed: SW1.1, U2.25
RST: C6.1, R4.2, SW2.1, U2.3
RXD: J6.4, U2.34
SCL: J7.3, R16.2, U2.36, U7.2
SDA: J7.4, R17.2, U2.33, U7.1
TXD: J6.3, U2.35

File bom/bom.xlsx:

| References | lcsc_min_qty | lcsc_part_number | mfr_part_number | package | Value | Footprint | Quantity | Total (5)
1 | C2, C3, C5, C6 | 100 | C128353 | 0805B104K250 | 0805 | 100n | C_0805_2012Metric | 4 | 20
2 | C1, C4 | 20 | C15850 | CL21A106KAYNNNE | 0805 | 10uF | C_0805_2012Metric | 2 | 10
3 | R4, R5, R6, R7, R8, R9 | 100 | C15401 | 0603WAJ0103T5E | 0603 | 10k | R_0603_1608Metric | 6 | 30
4 | R16, R17 | 100 | C384262 | WR06X222 JTL | 0603 | 2.2k | R_0603_1608Metric | 2 | 10
5 | R10, R12, R14 | 20 | C312247 | RTT031003BTP | 0603 | 100k | R_0603_1608Metric | 3 | 15
6 | R11 | 20 | C326751 | RT0603BRE0727KL | 0603 | 27k | R_0603_1608Metric | 1 | 5
7 | R13, R15 | 20 | C326751 | https://lcsc.com/product-detail/Others_YAGEO-RT0603BRE0727KL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 | 0603 | 27k | R_0603_1608Metric | 2 | 10
8 | R1, R2, R3 | 50 | C304726 | RS-03K2551FT | 0603 | 2.55K | LED_0603_1608Metric | 3 | 15
9 | D1 | 20 | C72044 | 19-217/R6C-AL1M2VY/3T | 0603 | AUX1 LED | LED_0603_1608Metric | 1 | 5
10 | D2 | 20 | C72044 | 19-217/R6C-AL1M2VY/3T | 0603 | MAIN LED | LED_0603_1608Metric | 1 | 5
11 | D3 | 20 | C72044 | 19-217/R6C-AL1M2VY/3T | 0603 | AUX2 LED | LED_0603_1608Metric | 1 | 5
12 | U3, U4, U5, U6 |  |  | ACS781LLRTR-050B-T | 7-PSOF | ACS781LLRTR-050B | Allegro_PSOF-7_4.8x6.4mm_P1.60mm | 4 | 20
13 | U7 | 1 | C34565 | LM75BD,118 | SOIC-8-150 | LM75BDP,118 | SO-8_3.9x4.9mm_P1.27mm | 1 | 5
14 | U2 | 1 | C473012 | ESP32-WROOM-32D | SMD-38 | ESP32-WROOM-32D | ESP32-WROOM-32 | 1 | 5
15 | U1 | 5 | C81100 | ME6119C33M5G | SOT23-5 | ME6119C33M5G | SOT-23-5 | 1 | 5
16 | SW1 | 10 | C111373 | TS-1102W-4316 | 6x6x4.3 | TS-1102W-4316 | SW_Push_1P1T_NO_6x6mm_H9.5mm | 1 | 5
17 | Q1, Q2, Q3, Q4 |  |  | BSC070N10LS5 |  | BSC070N10LS5 | TDSON-8-1 | 4 | 20
